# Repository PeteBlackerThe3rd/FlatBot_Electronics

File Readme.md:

KiCAD PCB design files for the FlatBot controller board.

Mostly this board just connects different parts together. It's got some level shifters and power regulators.

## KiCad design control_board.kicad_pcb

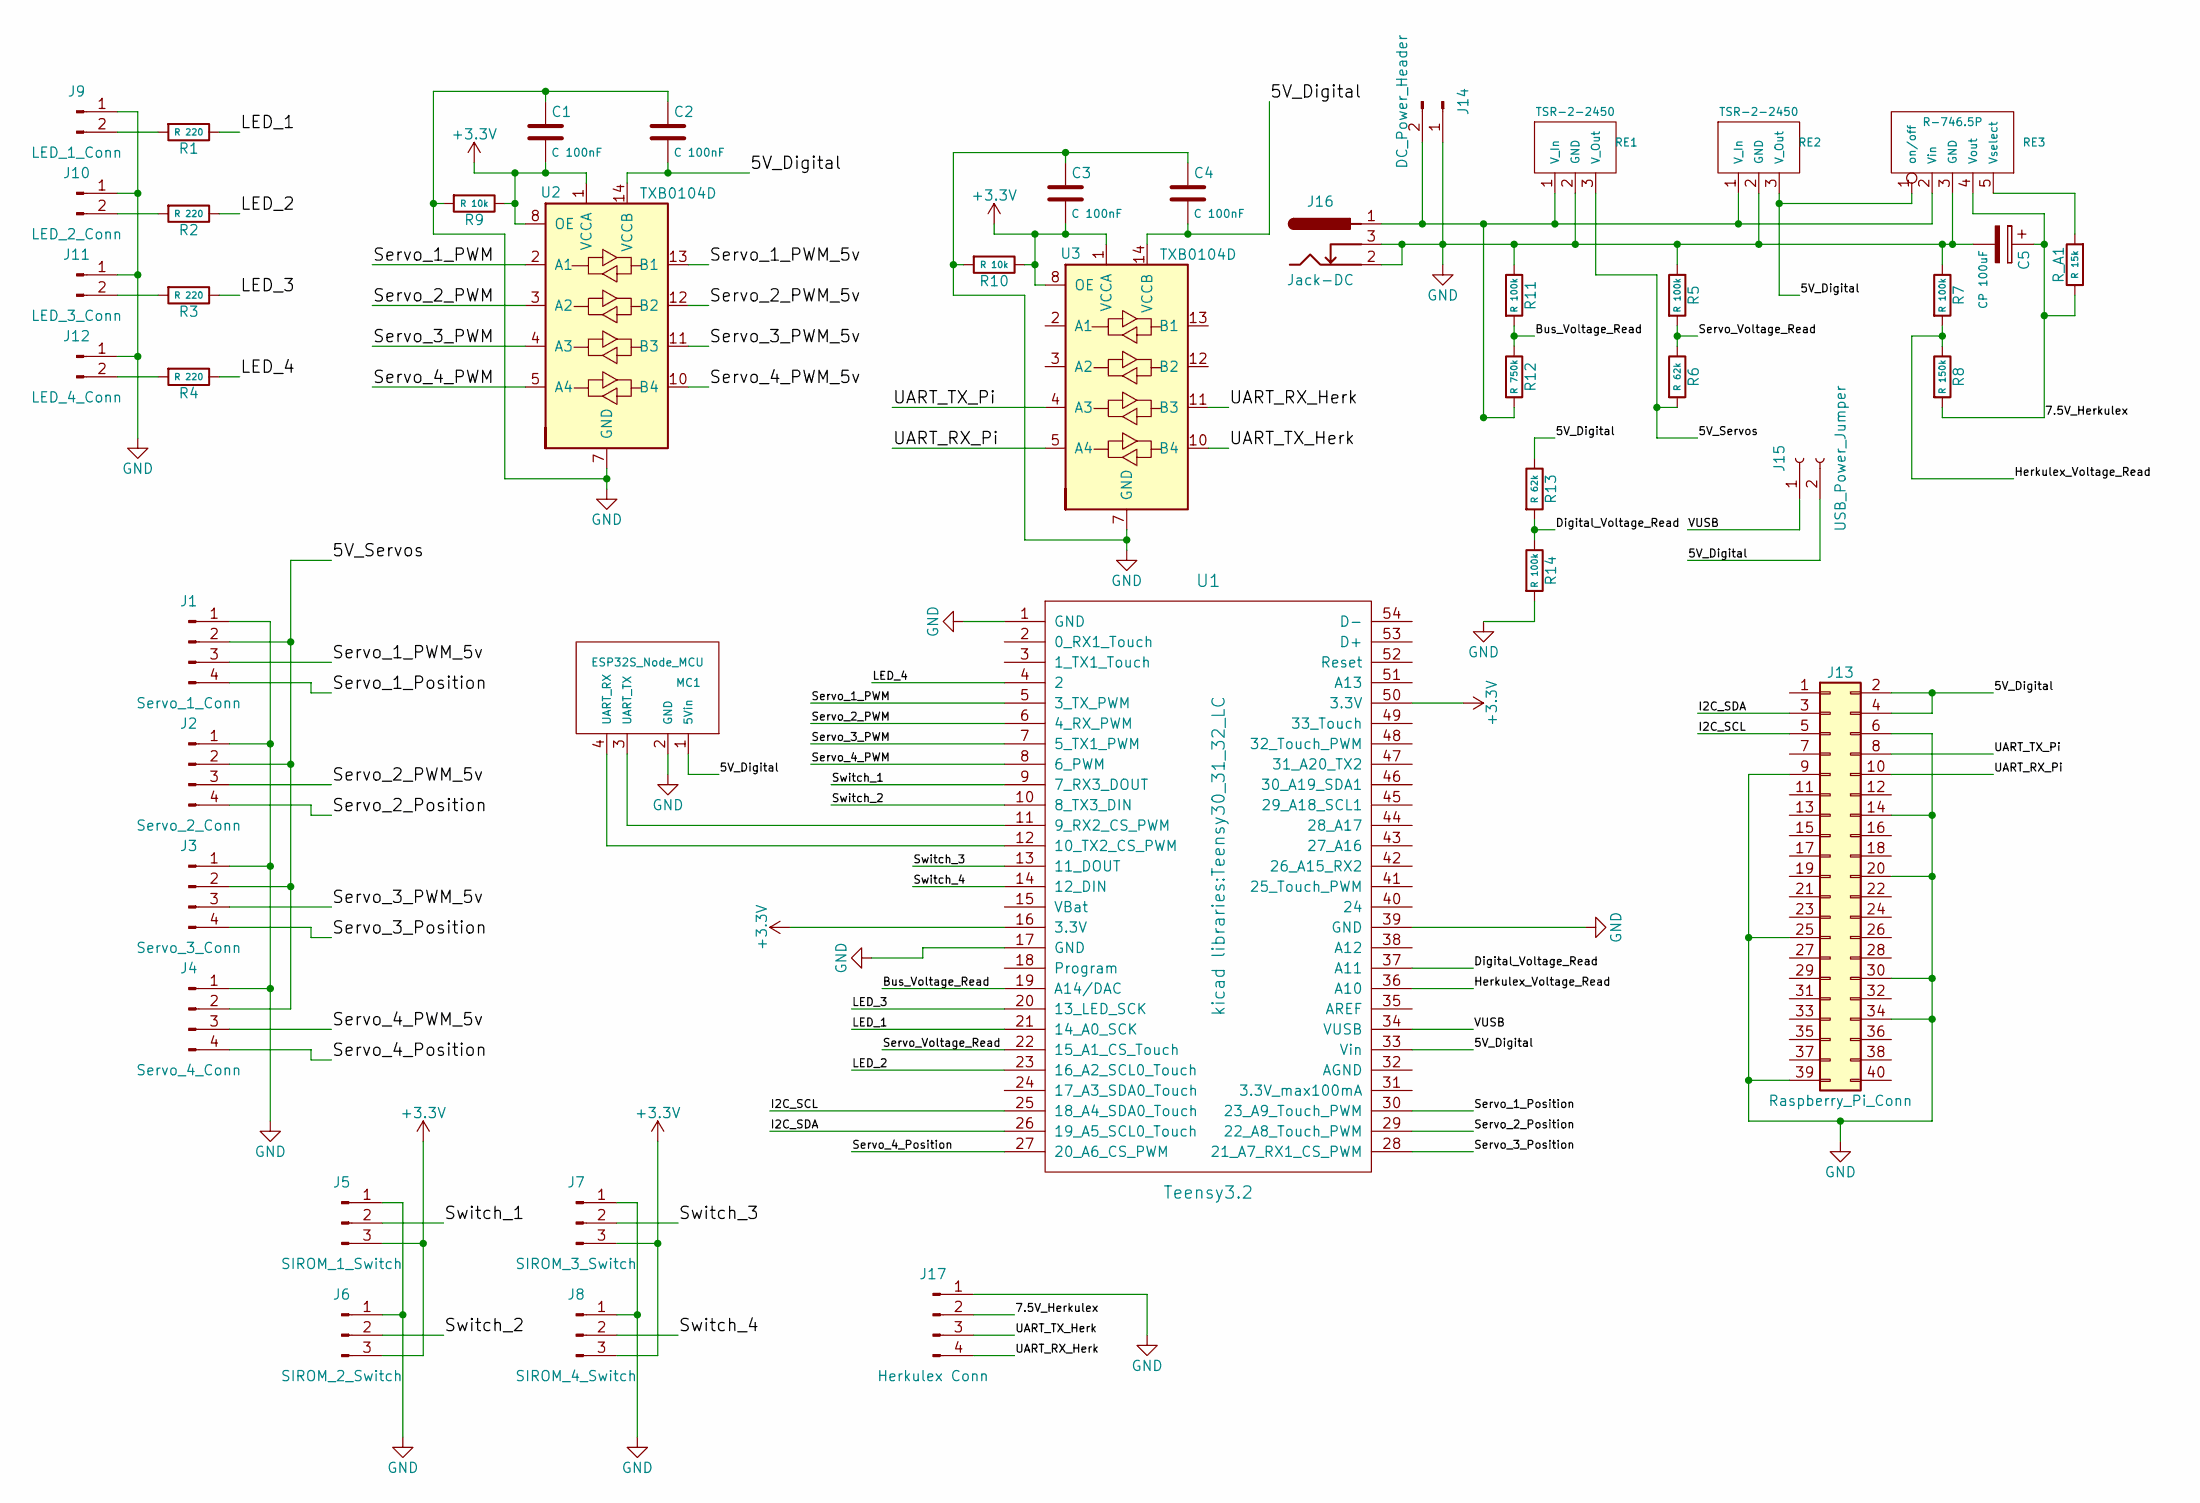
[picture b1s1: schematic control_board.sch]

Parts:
C1, C2, C3, C4: C 100nF; C_1206_HandSoldering
C5: CP 100uF; CP_Radial_D5.0mm_P2.50mm
J1: Servo_1_Conn; SL-104-X-XX_1x04
J2: Servo_2_Conn; SL-104-X-XX_1x04
J3: Servo_3_Conn; SL-104-X-XX_1x04
J4: Servo_4_Conn; SL-104-X-XX_1x04
J5: SIROM_1_Switch; SL-103-X-XX_1x03
J6: SIROM_2_Switch; SL-103-X-XX_1x03
J7: SIROM_3_Switch; SL-103-X-XX_1x03
J8: SIROM_4_Switch; SL-103-X-XX_1x03
J9: LED_1_Conn; SL-102-X-XX_1x02
J10: LED_2_Conn; SL-102-X-XX_1x02
J11: LED_3_Conn; SL-102-X-XX_1x02
J12: LED_4_Conn; SL-102-X-XX_1x02
J13: Raspberry_Pi_Conn; PI_GPIO_Reversed
J14: DC_Power_Header; SL-102-X-XX_1x02
J15: USB_Power_Jumper
J16: Jack-DC; 2_5mm_DC_jack_SMD
J17: Herkulex Conn; SL-104-X-XX_1x04
MC1: ESP32S_Node_MCU; ESP32S_Node_MCU_Edge
R1, R2, R3, R4: R 220; R_1206_HandSoldering
R5, R7, R11, R14: R 100k; R_1206_HandSoldering
R6, R13: R 62k; R_1206_HandSoldering
R8: R 150k; R_1206_HandSoldering
R9, R10: R 10k; R_1206_HandSoldering
R12: R 750k; R_1206_HandSoldering
RE1, RE2: TSR-2-2450; TSR-series
RE3: R-746.5P; Recom-Adjustable
R_A1: R 15k; R_1206_HandSoldering
U1: Teensy3.2; Teensy30_31_32_LC
U2, U3: TXB0104D; SOIC-14_3.9x8.7mm_Pitch1.27mm

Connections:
+3V3: C1.2, C3.2, J5.3, J6.3, J7.3, J8.3, R9.1, R10.1, U1.16 (3.3V), U1.50 (3.3V), U2.1 (VCCA), U2.8 (OE), U3.1 (VCCA), U3.8 (OE)
/5V_Digital: C2.2, C4.2, J13.2, J13.4, J15.2, MC1.1 (5Vin), R13.1, RE2.3 (V_Out), RE3.1 (on/off), U1.33 (Vin), U2.14 (VCCB), U3.14 (VCCB)
/5V_Servos: J1.2, J2.2, J3.2, J4.2, R6.2, RE1.3 (V_Out)
/7.5V_Herkulex: C5.1, J17.2, R8.2, RE3.4 (Vout), R_A1.1
/Bus_Voltage_Read: R11.2, R12.1, U1.19 (A14/DAC)
/Digital_Voltage_Read: R13.2, R14.1, U1.37 (A11)
/Herkulex_Voltage_Read: R7.2, R8.1, U1.36 (A10)
/I2C_SCL: J13.5, U1.25 (18_A4_SDA0_Touch)
/I2C_SDA: J13.3, U1.26 (19_A5_SCL0_Touch)
/LED_1: R1.1, U1.21 (14_A0_SCK)
/LED_2: R2.1, U1.23 (16_A2_SCL0_Touch)
/LED_3: R3.1, U1.20 (13_LED_SCK)
/LED_4: R4.1, U1.4 (2)
/Servo_1_PWM: U1.5 (3_TX_PWM), U2.2 (A1)
/Servo_1_PWM_5v: J1.3, U2.13 (B1)
/Servo_1_Position: J1.4, U1.30 (23_A9_Touch_PWM)
/Servo_2_PWM: U1.6 (4_RX_PWM), U2.3 (A2)
/Servo_2_PWM_5v: J2.3, U2.12 (B2)
/Servo_2_Position: J2.4, U1.29 (22_A8_Touch_PWM)
/Servo_3_PWM: U1.7 (5_TX1_PWM), U2.4 (A3)
/Servo_3_PWM_5v: J3.3, U2.11 (B3)
/Servo_3_Position: J3.4, U1.28 (21_A7_RX1_CS_PWM)
/Servo_4_PWM: U1.8 (6_PWM), U2.5 (A4)
/Servo_4_PWM_5v: J4.3, U2.10 (B4)
/Servo_4_Position: J4.4, U1.27 (20_A6_CS_PWM)
/Servo_Voltage_Read: R5.2, R6.1, U1.22 (15_A1_CS_Touch)
/Switch_1: J5.2, U1.9 (7_RX3_DOUT)
/Switch_2: J6.2, U1.10 (8_TX3_DIN)
/Switch_3: J7.2, U1.13 (11_DOUT)
/Switch_4: J8.2, U1.14 (12_DIN)
/UART_RX_Herk: J17.4, U3.11 (B3)
/UART_RX_Pi: J13.10, U3.5 (A4)
/UART_TX_Herk: J17.3, U3.10 (B4)
/UART_TX_Pi: J13.8, U3.4 (A3)
/VUSB: J15.1, U1.34 (VUSB)
GND: C1.1, C2.1, C3.1, C4.1, C5.2, J1.1, J2.1, J3.1, J4.1, J5.1, J6.1, J7.1, J8.1, J9.1, J10.1, J11.1, J12.1, J13.6, J13.9, J13.14, J13.20, J13.25, J13.30, J13.34, J13.39, J14.1, J16.2, J16.3, J17.1, MC1.2 (GND), R5.1, R7.1, R9.2, R10.2, R11.1, R14.2, RE1.2 (GND), RE2.2 (GND), RE3.3 (GND), U1.1 (GND), U1.17 (GND), U1.39 (GND), U2.7 (GND), U3.7 (GND)
unnamed: J9.2, R1.2
unnamed: J10.2, R2.2
unnamed: J11.2, R3.2
unnamed: J12.2, R4.2
unnamed: J14.2, J16.1, R12.2, RE1.1 (V_In), RE2.1 (V_In), RE3.2 (Vin)
unnamed: MC1.3 (UART_TX), U1.11 (9_RX2_CS_PWM)
unnamed: MC1.4 (UART_RX), U1.12 (10_TX2_CS_PWM)
unnamed: RE3.5 (Vselect), R_A1.2

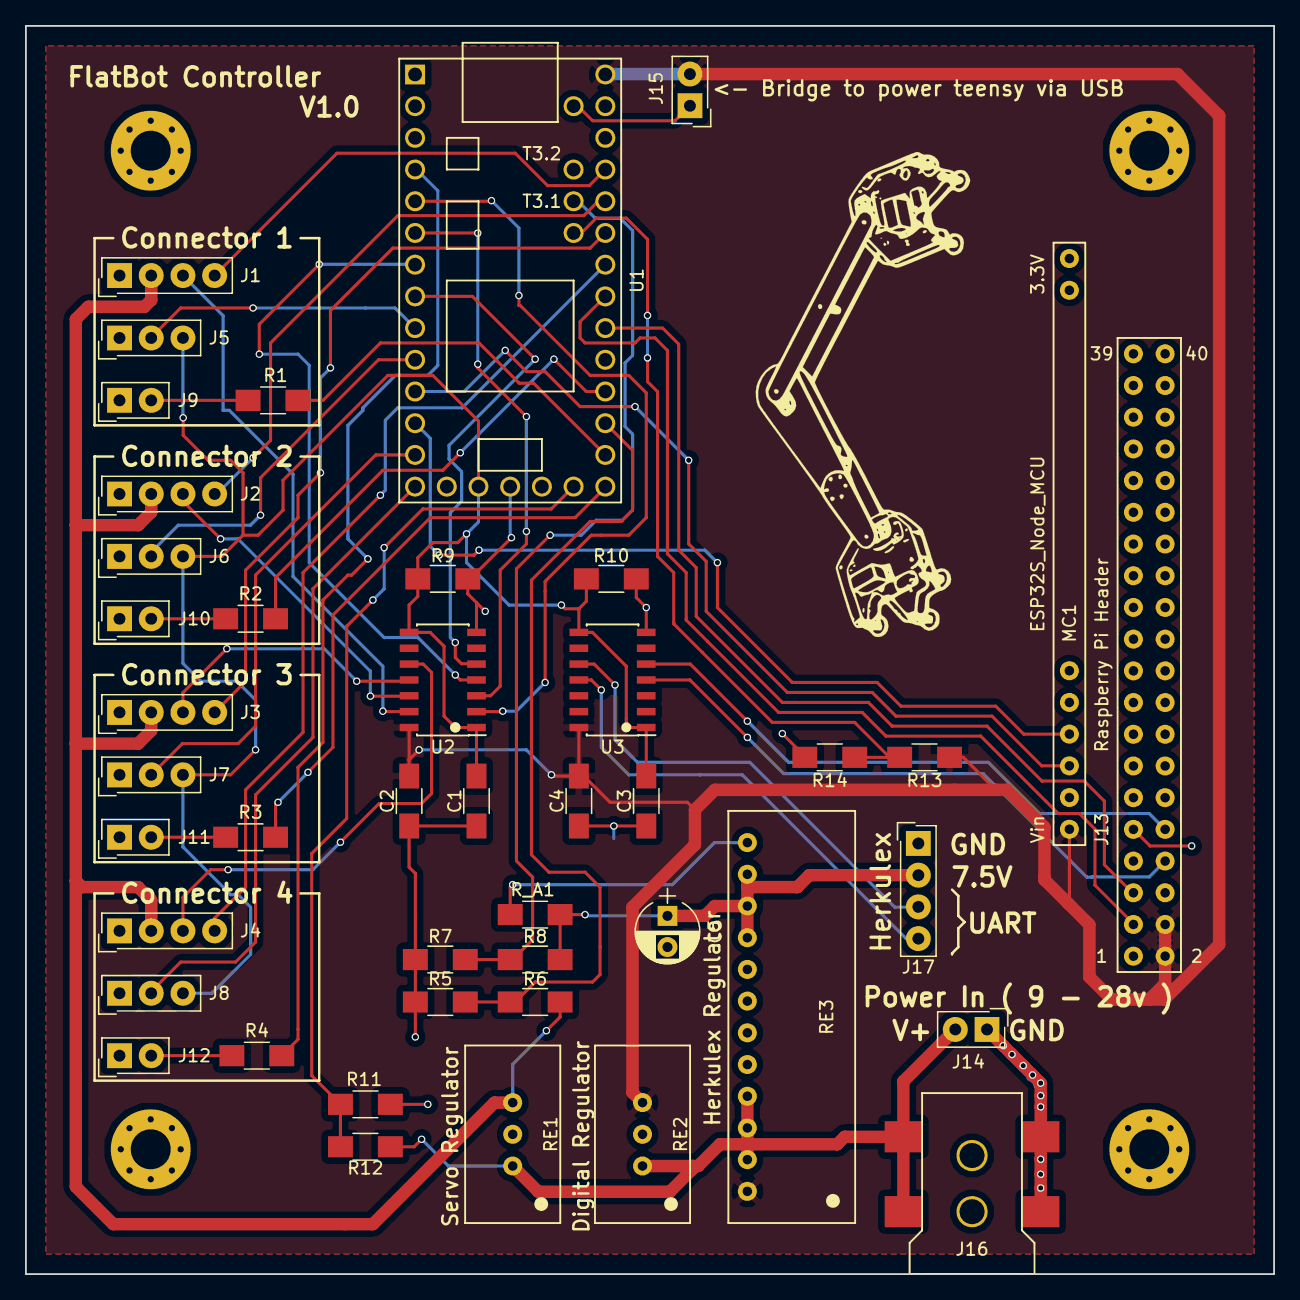
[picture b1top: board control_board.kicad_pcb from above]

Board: 2 copper layers, 100.0 x 100.0 mm, 44 parts (0 on the bottom side), 44 nets.

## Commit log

2018-12-18 Added resistor values, correct 7.5V reg enable pin and output cap
